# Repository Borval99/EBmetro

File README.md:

# EBmetro

## Descrizione

Il progetto riguarda la ricostruzione di un **misuratore di campi elettrici e magnetici (EBmetro)** ideato dal Prof. Francesco Dalla Valle.

Lo strumento è stato progettato per rendere **misurabili e osservabili**:

* intensità del campo elettrico e magnetico
* direzione
* verso

con l’obiettivo di fornire un supporto concreto alla comprensione dell’elettromagnetismo.

---

## Obiettivo

L’EBmetro permette di verificare sperimentalmente:

* la circuitazione del campo elettrico lungo una linea chiusa
* la circuitazione del campo magnetico
* il fenomeno dell’induzione elettromagnetica

rendendo osservabili in modo diretto le prime tre equazioni di Maxwell.

---

## Struttura della repository

### /3D Model

Contiene i modelli dei case utilizzati per ospitare il microcontrollore e la scheda di acquisizione.

Sono presenti due principali varianti:

* versione per stampa 3D
* versione per taglio laser

La versione realizzata tramite intaglio laser consente una produzione più rapida e semplificata.

---

### /EBmetro

Contiene l’implementazione completa del dispositivo:

* schemi elettronici
* PCB
* firmware

Dove sono presenti le schede per l'EBmetro e per la base dell'EBmetro.

---

### /generatore

Contiene lo sviluppo di un generatore di rampe di corrente:

* schema elettronico
* firmware

Il generatore è in grado di fornire correnti fino a 30 A ed è utilizzato per pilotare bobine di Helmholtz.
Questo consente di generare campi magnetici controllati e misurare, tramite il sensore (“manico”), l’andamento della corrente indotta in un avvolgimento di dimensioni variabili.

---

## Descrizione del funzionamento

Il dispositivo consente la misura del campo elettrico o magnetico in funzione:

* della testina installata
* delle impostazioni software

L’elemento principale è una **testina rotante** dotata di contatti in oro, che ruota sul proprio asse.

I contatti sono stati realizzati tramite PCB, HASL con placcatura.

Durante la rotazione, la testina entra in contatto con due **contatti striscianti**, permettendo l’acquisizione del segnale.

L’elaborazione del segnale avviene in un’unità separata dalla base, al fine di ridurre le interferenze sulla misura.

Nella base dell’EBmetro è possibile integrare:

* un motore brushless
* oppure un motore passo-passo

entrambi controllati da un microcontrollore ATtiny85 posizionato sotto la struttura.

L'EBmetro ha inoltre un Goniometro sulla propria base.

---

## Crediti

Ideato dal:

* Prof. Francesco Dalla Valle
* Prof. Giacomoni
* Prof. Cortesi

Sviluppo di questa versione:

* Enzo Cortesi
* Ing. Valerio Borghi
* FabLab Maker Station Bassa Romagna

---

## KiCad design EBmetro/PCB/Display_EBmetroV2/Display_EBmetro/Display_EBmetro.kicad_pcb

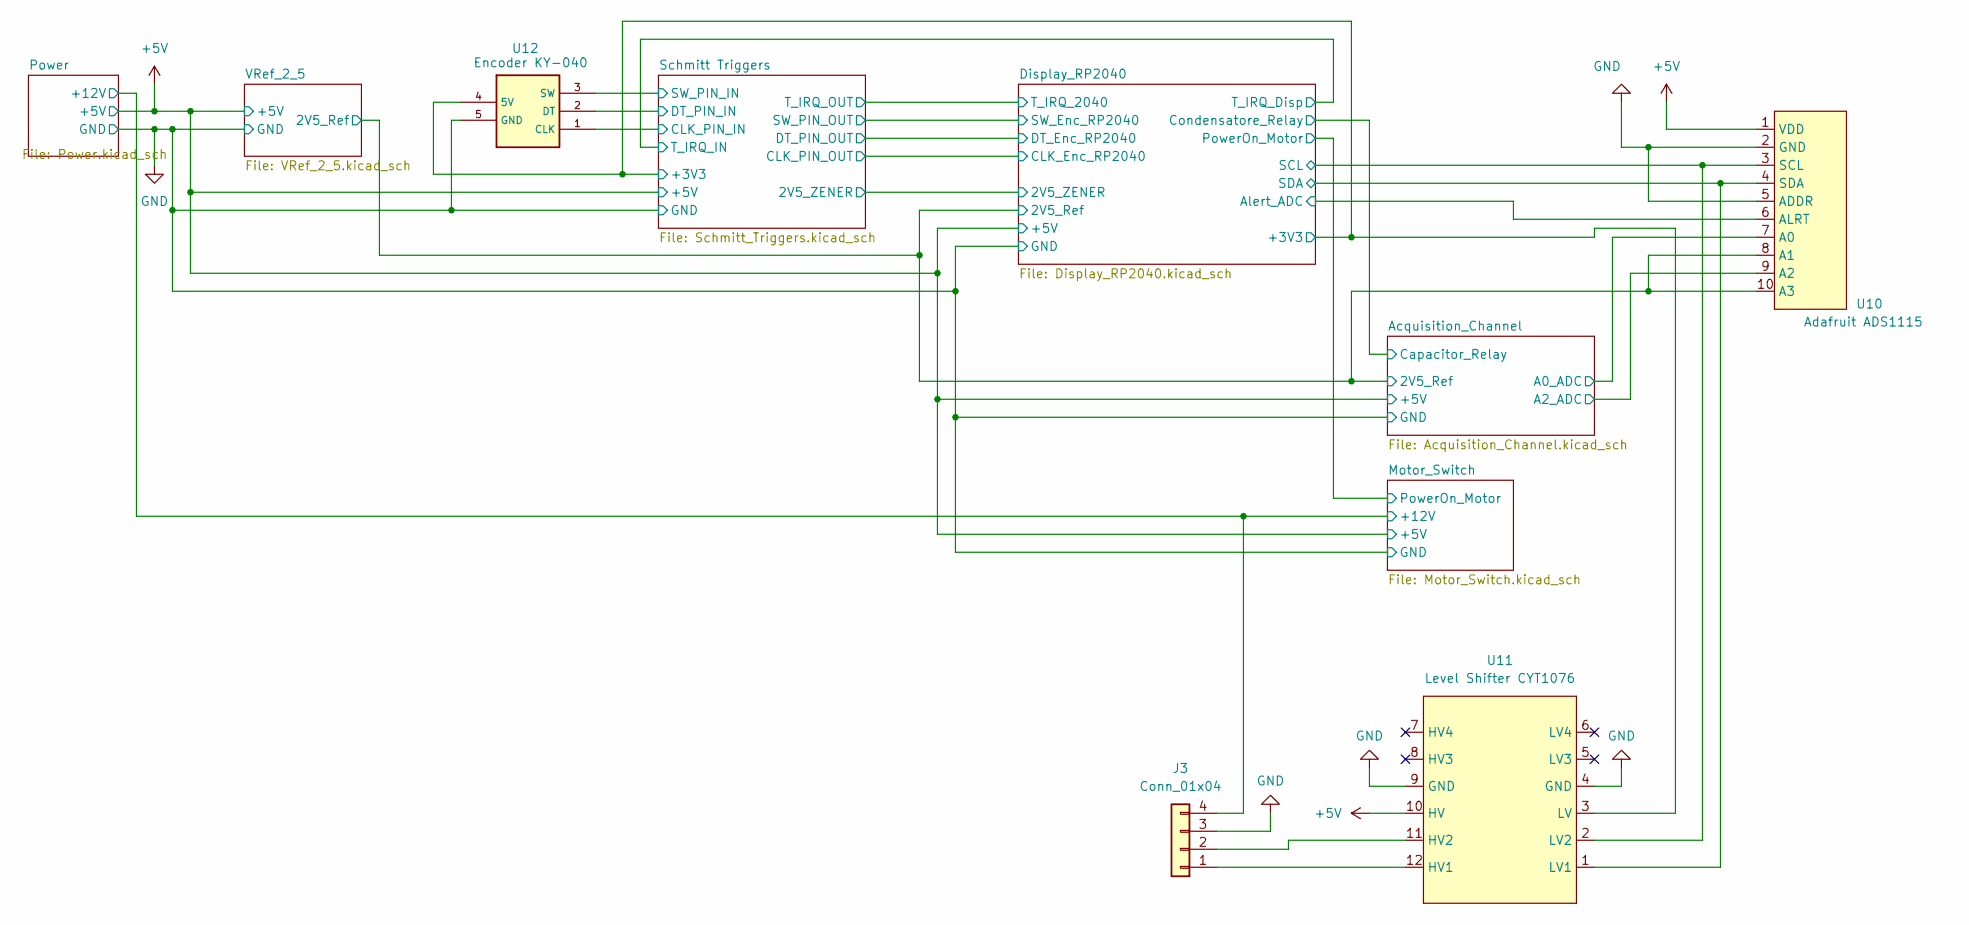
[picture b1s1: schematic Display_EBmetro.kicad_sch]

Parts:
J3: Conn_01x04; JST_EH_B4B-EH-A_1x04_P2.50mm_Vertical
U10: Adafruit ADS1115; PinSocket_1x10_P2.54mm_Vertical
U11: Level Shifter CYT1076; LevelShifter_CYT1076
U12: Encoder KY-040; Encoder_KY-040

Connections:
+5V: U10.1 (VDD), U11.10 (HV); also elsewhere on the board
+12V: J3.4; also elsewhere on the board
/Acquisition_Channel/2V5_Ref: U10.8 (A1), U10.10 (A3); also elsewhere on the board
/Acquisition_Channel/A0_ADC: U10.7 (A0); also elsewhere on the board
/Acquisition_Channel/A2_ADC: U10.9 (A2); also elsewhere on the board
/Display_RP2040/+3V3: U11.3 (LV), U12.4 (5V); also elsewhere on the board
/Display_RP2040/Alert_ADC: U10.6 (ALRT); also elsewhere on the board
/Display_RP2040/SCL: U10.3 (SCL), U11.2 (LV2); also elsewhere on the board
/Display_RP2040/SDA: U10.4 (SDA), U11.1 (LV1); also elsewhere on the board
/Schmitt Triggers/CLK_PIN_IN: U12.1 (CLK); also elsewhere on the board
/Schmitt Triggers/DT_PIN_IN: U12.2 (DT); also elsewhere on the board
/Schmitt Triggers/SW_PIN_IN: U12.3 (SW); also elsewhere on the board
GND: J3.3, U10.2 (GND), U10.5 (ADDR), U11.4 (GND), U11.9 (GND), U12.5 (GND); also elsewhere on the board
unnamed: J3.1, U11.12 (HV1)
unnamed: J3.2, U11.11 (HV2)

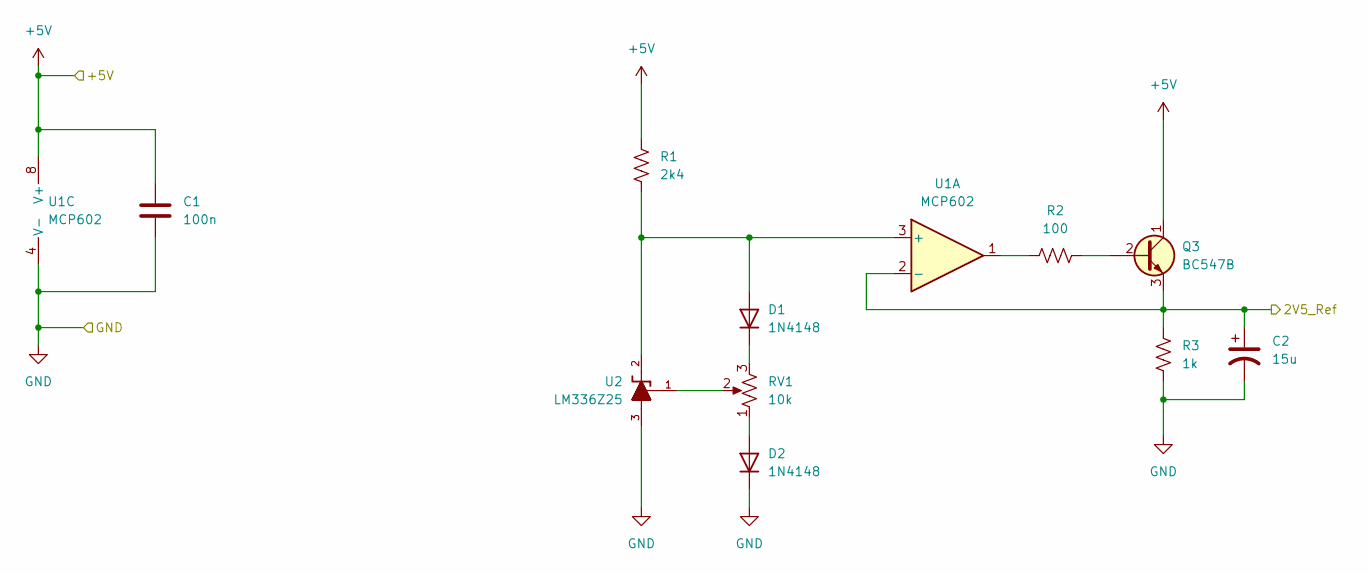
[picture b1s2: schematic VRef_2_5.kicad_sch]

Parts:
C1: 100n; C_Rect_L7.2mm_W2.5mm_P5.00mm_FKS2_FKP2_MKS2_MKP2
C2: 15u; CP_Radial_Tantal_D5.5mm_P5.00mm
D1, D2: 1N4148; D_DO-35_SOD27_P7.62mm_Horizontal
Q3: BC547B; TO-92_Inline_Wide_CBE
R1: 2k4; R_Axial_DIN0207_L6.3mm_D2.5mm_P10.16mm_Horizontal
R2: 100; R_Axial_DIN0207_L6.3mm_D2.5mm_P10.16mm_Horizontal
R3: 1k; R_Axial_DIN0207_L6.3mm_D2.5mm_P10.16mm_Horizontal
RV1: 10k; Potentiometer_Bourns_3296W_Vertical
U1: MCP602; DIP-8_W7.62mm_Socket
U2: LM336Z25; TO-92L_Inline_Wide

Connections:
+5V: C1.2, Q3.1 (C), R1.1, U1.8 (V+); also elsewhere on the board
/Acquisition_Channel/2V5_Ref: C2.1, Q3.3 (E), R3.1, U1.2 (-); also elsewhere on the board
GND: C1.1, C2.2, D2.1 (K), R3.2, U1.4 (V-), U2.3; also elsewhere on the board
unnamed: D1.2 (A), R1.2, U1.3 (+), U2.2
unnamed: D1.1 (K), RV1.3
unnamed: D2.2 (A), RV1.1
unnamed: Q3.2 (B), R2.2
unnamed: R2.1, U1.1
unnamed: RV1.2, U2.1

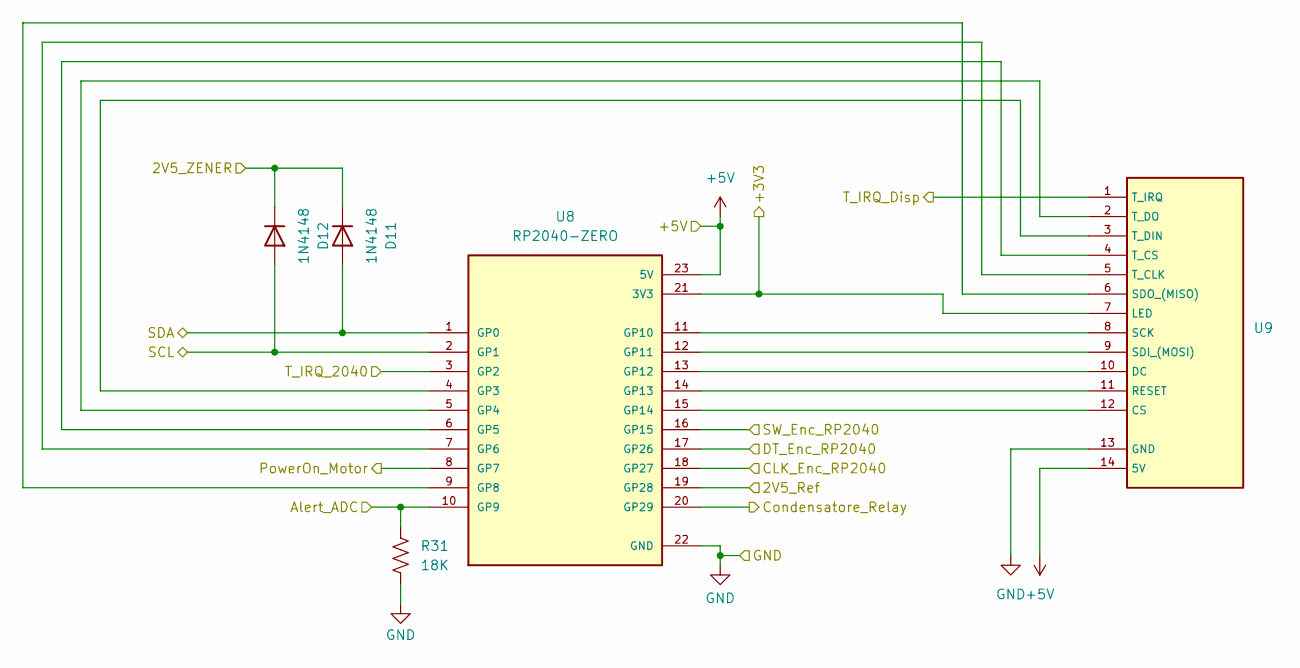
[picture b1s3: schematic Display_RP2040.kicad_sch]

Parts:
D11, D12: 1N4148; D_DO-35_SOD27_P7.62mm_Horizontal
R31: 18K; R_Axial_DIN0207_L6.3mm_D2.5mm_P10.16mm_Horizontal
U8: RP2040-ZERO; MODULE_RP2040-ZERO_V2; PARTREV NA
U9: Display_TFT_LCD_4

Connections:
+5V: U8.23 (5V), U9.14 (5V); also elsewhere on the board
/Acquisition_Channel/2V5_Ref: U8.19 (GP28); also elsewhere on the board
/Acquisition_Channel/Capacitor_Relay: U8.20 (GP29); also elsewhere on the board
/Display_RP2040/+3V3: U8.21 (3V3), U9.7 (LED); also elsewhere on the board
/Display_RP2040/Alert_ADC: R31.1, U8.10 (GP9); also elsewhere on the board
/Display_RP2040/CLK_Enc_RP2040: U8.18 (GP27); also elsewhere on the board
/Display_RP2040/DT_Enc_RP2040: U8.17 (GP26); also elsewhere on the board
/Display_RP2040/PowerOn_Motor: U8.8 (GP7); also elsewhere on the board
/Display_RP2040/SCL: D12.2 (A), U8.2 (GP1); also elsewhere on the board
/Display_RP2040/SDA: D11.2 (A), U8.1 (GP0); also elsewhere on the board
/Display_RP2040/SW_Enc_RP2040: U8.16 (GP15); also elsewhere on the board
/Display_RP2040/T_IRQ_2040: U8.3 (GP2); also elsewhere on the board
/Display_RP2040/T_IRQ_Disp: U9.1 (T_IRQ); also elsewhere on the board
/Schmitt Triggers/2V5_ZENER: D11.1 (K), D12.1 (K); also elsewhere on the board
GND: R31.2, U8.22 (GND), U9.13 (GND); also elsewhere on the board
unnamed: U8.4 (GP3), U9.3 (T_DIN)
unnamed: U8.5 (GP4), U9.2 (T_DO)
unnamed: U8.6 (GP5), U9.4 (T_CS)
unnamed: U8.7 (GP6), U9.5 (T_CLK)
unnamed: U8.9 (GP8), U9.6 (SDO_(MISO))
unnamed: U8.11 (GP10), U9.8 (SCK)
unnamed: U8.12 (GP11), U9.9 (SDI_(MOSI))
unnamed: U8.13 (GP12), U9.10 (DC)
unnamed: U8.14 (GP13), U9.11 (RESET)
unnamed: U8.15 (GP14), U9.12 (CS)

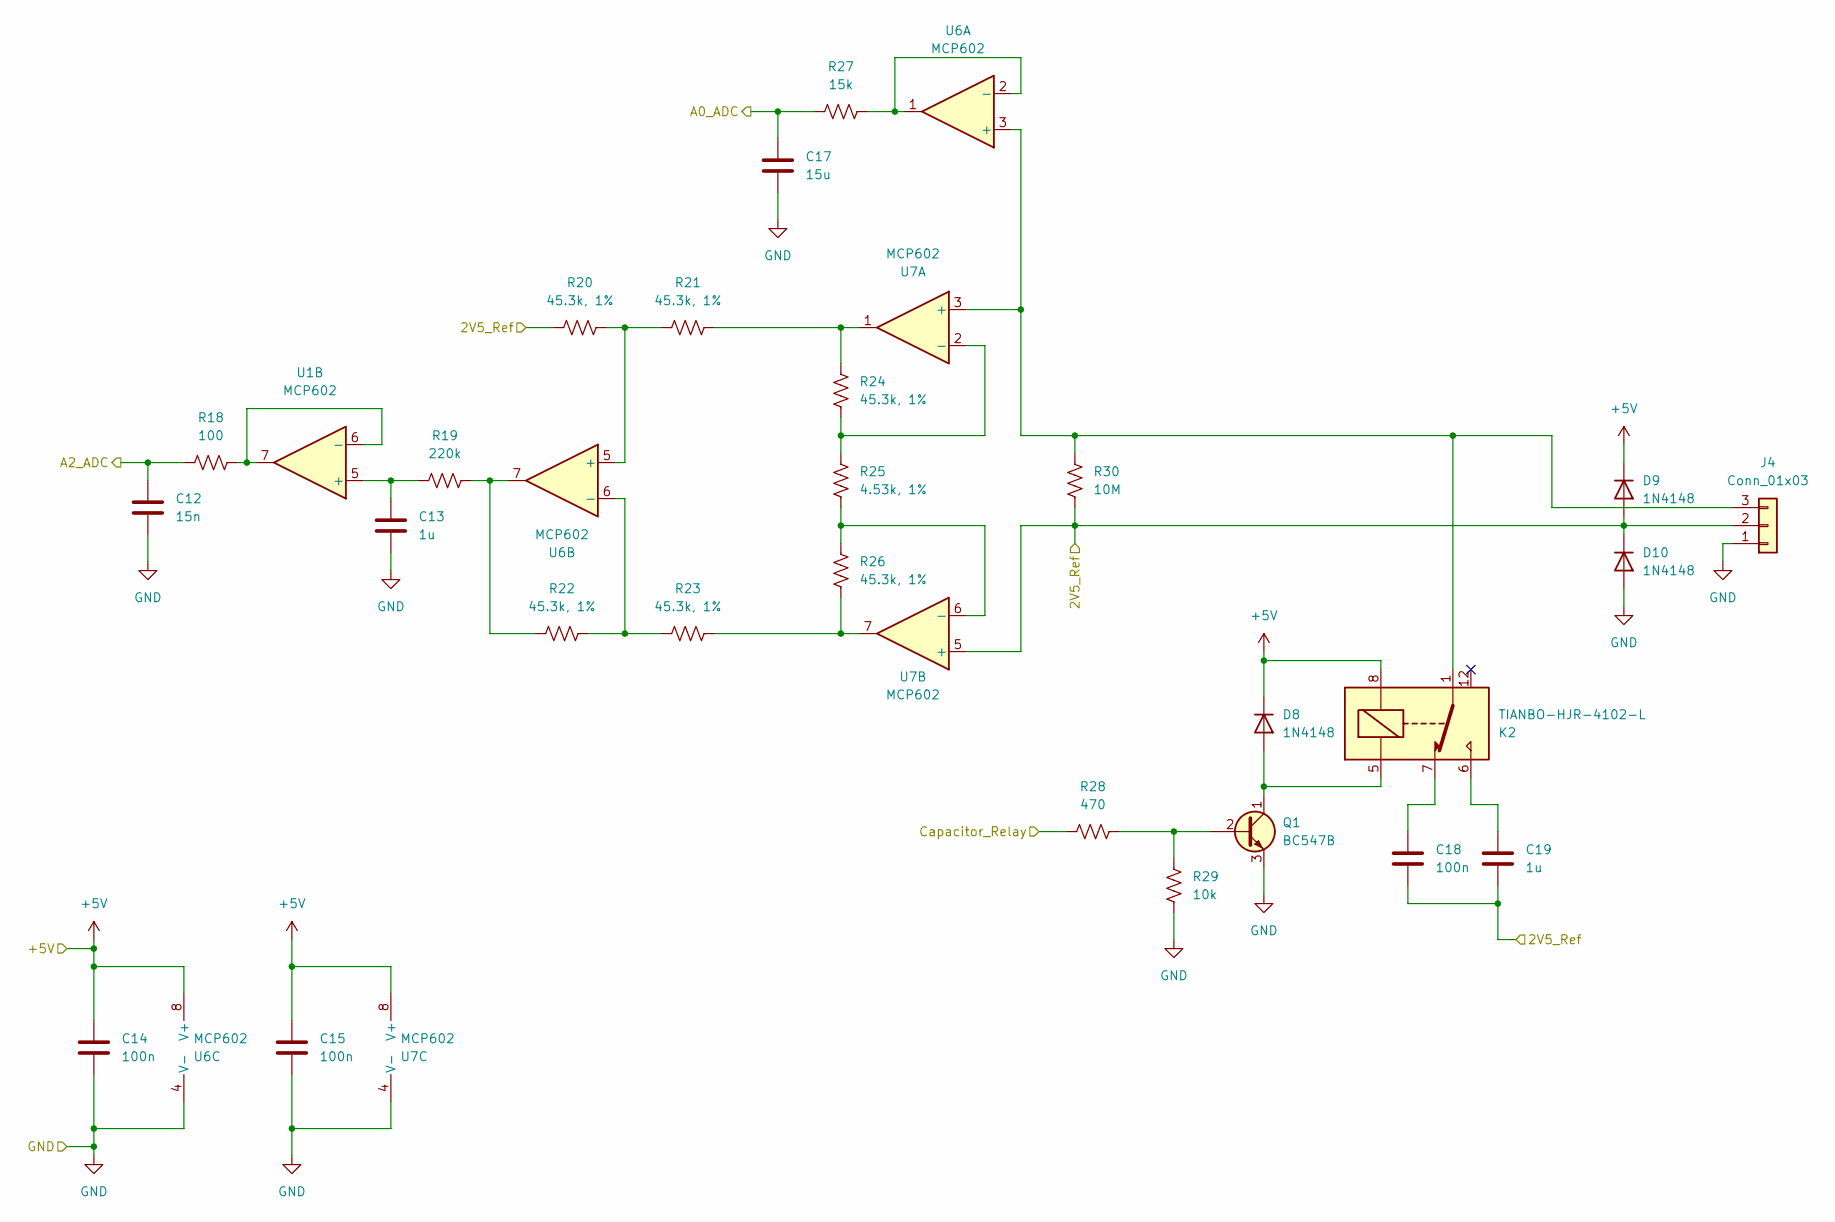
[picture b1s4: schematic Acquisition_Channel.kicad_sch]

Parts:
C12: 15n; C_Rect_L7.2mm_W2.5mm_P5.00mm_FKS2_FKP2_MKS2_MKP2
C13, C19: 1u; C_Rect_L7.2mm_W5.5mm_P5.00mm_FKS2_FKP2_MKS2_MKP2
C14, C15, C18: 100n; C_Rect_L7.2mm_W2.5mm_P5.00mm_FKS2_FKP2_MKS2_MKP2
C17: 15u; C_Rect_L7.2mm_W2.5mm_P5.00mm_FKS2_FKP2_MKS2_MKP2
D8, D9, D10: 1N4148; D_DO-35_SOD27_P7.62mm_Horizontal
J4: Conn_01x03; JST_EH_B3B-EH-A_1x03_P2.50mm_Vertical
K2: TIANBO-HJR-4102-L; Relay_SPDT_HJR-4102
Q1: BC547B; TO-92_Inline_Wide_CBE
R18: 100; R_Axial_DIN0207_L6.3mm_D2.5mm_P10.16mm_Horizontal
R19: 220k; R_Axial_DIN0207_L6.3mm_D2.5mm_P10.16mm_Horizontal
R20, R21, R22, R23, R24, R26: 45.3k, 1%; R_Axial_DIN0207_L6.3mm_D2.5mm_P10.16mm_Horizontal
R25: 4.53k, 1%; R_Axial_DIN0207_L6.3mm_D2.5mm_P10.16mm_Horizontal
R27: 15k; R_Axial_DIN0207_L6.3mm_D2.5mm_P10.16mm_Horizontal
R28: 470; R_Axial_DIN0207_L6.3mm_D2.5mm_P10.16mm_Horizontal
R29: 10k; R_Axial_DIN0207_L6.3mm_D2.5mm_P10.16mm_Horizontal
R30: 10M; R_Axial_DIN0207_L6.3mm_D2.5mm_P10.16mm_Horizontal
U1, U6, U7: MCP602; DIP-8_W7.62mm_Socket

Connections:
+5V: C14.1, C15.1, D8.1 (K), D9.1 (K), K2.8, U6.8 (V+), U7.8 (V+); also elsewhere on the board
/Acquisition_Channel/2V5_Ref: C18.2, C19.2, D9.2 (A), D10.1 (K), J4.2, R20.1, R30.2, U7.5 (+); also elsewhere on the board
/Acquisition_Channel/A0_ADC: C17.1, R27.2; also elsewhere on the board
/Acquisition_Channel/A2_ADC: C12.1, R18.1; also elsewhere on the board
/Acquisition_Channel/Capacitor_Relay: R28.2; also elsewhere on the board
GND: C12.2, C13.2, C14.2, C15.2, C17.2, D10.2 (A), J4.1, Q1.3 (E), R29.2, U6.4 (V-), U7.4 (V-); also elsewhere on the board
unnamed: C18.1, K2.7
unnamed: C19.1, K2.6
unnamed: D8.2 (A), K2.5, Q1.1 (C)
unnamed: J4.3, K2.1, R30.1, U6.3 (+), U7.3 (+)
unnamed: Q1.2 (B), R28.1, R29.1
unnamed: R19.2, R22.1, U6.7
unnamed: R21.2, R24.2, U7.1
unnamed: R23.2, R26.1, U7.7
unnamed: C13.1, R19.1, U1.5 (+)
unnamed: R18.2, U1.6 (-), U1.7
unnamed: R27.1, U6.1, U6.2 (-)
unnamed: R20.2, R21.1, U6.5 (+)
unnamed: R22.2, R23.1, U6.6 (-)
unnamed: R24.1, R25.2, U7.2 (-)
unnamed: R25.1, R26.2, U7.6 (-)

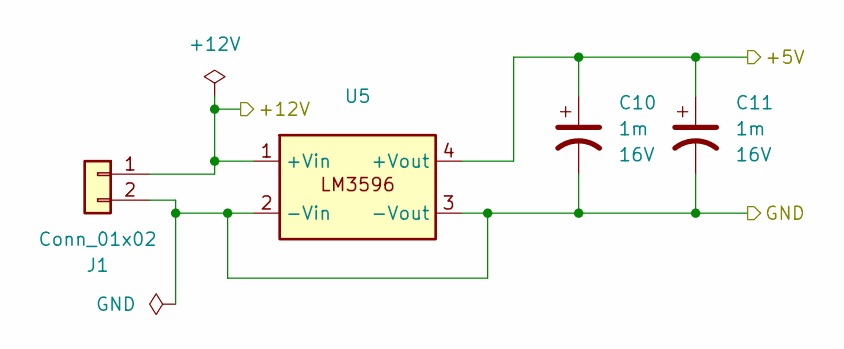
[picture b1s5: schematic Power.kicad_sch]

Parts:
C10, C11: 1m; CP_Radial_D10.0mm_P5.00mm; Voltage 16V
J1: Conn_01x02; JST_EH_B2B-EH-A_1x02_P2.50mm_Vertical
U5: LM3596

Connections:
+5V: C10.1, C11.1, U5.4 (+Vout); also elsewhere on the board
+12V: J1.1, U5.1 (+Vin); also elsewhere on the board
GND: C10.2, C11.2, J1.2, U5.2 (-Vin), U5.3 (-Vout); also elsewhere on the board

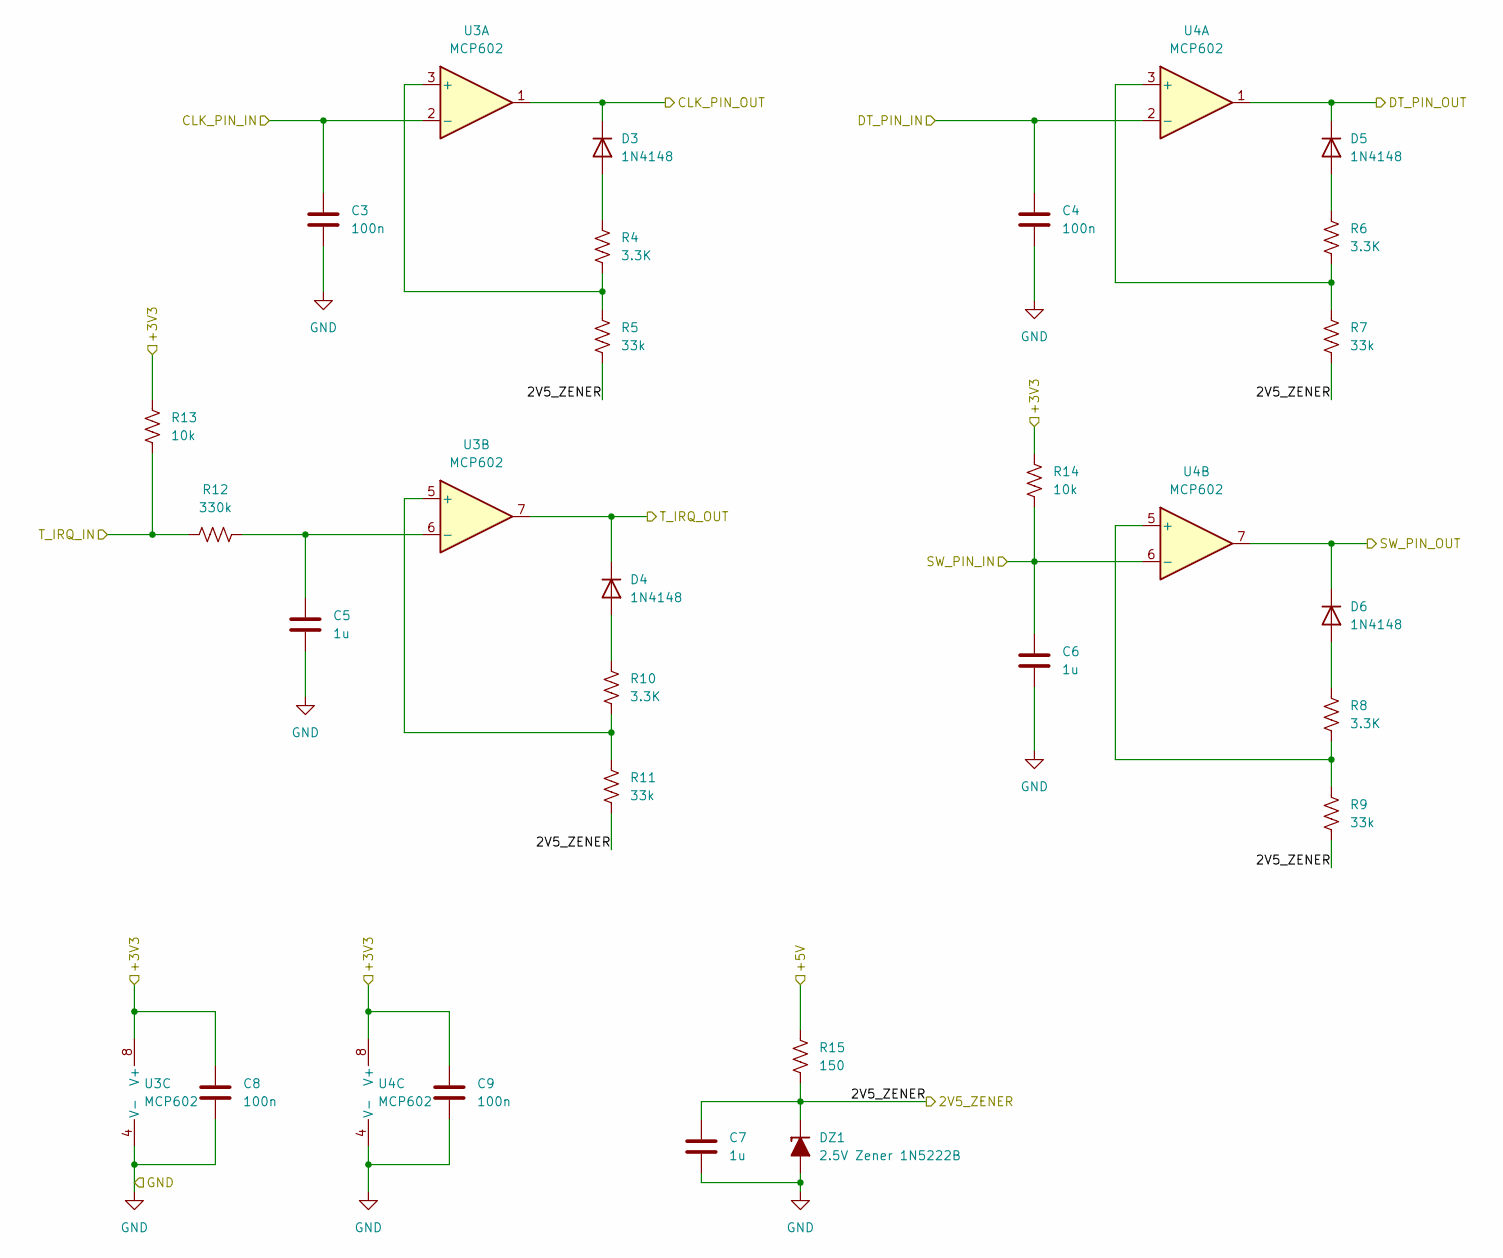
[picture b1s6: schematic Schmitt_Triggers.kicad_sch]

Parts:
C3, C4, C8, C9: 100n; C_Rect_L7.2mm_W2.5mm_P5.00mm_FKS2_FKP2_MKS2_MKP2
C5, C6, C7: 1u; C_Rect_L7.2mm_W5.5mm_P5.00mm_FKS2_FKP2_MKS2_MKP2
D3, D4, D5, D6: 1N4148; D_DO-35_SOD27_P7.62mm_Horizontal
DZ1: 2.5V Zener 1N5222B; D_DO-35_SOD27_P10.16mm_Horizontal_Zener
R4, R6, R8, R10: 3.3K; R_Axial_DIN0207_L6.3mm_D2.5mm_P10.16mm_Horizontal
R5, R7, R9, R11: 33k; R_Axial_DIN0207_L6.3mm_D2.5mm_P10.16mm_Horizontal
R12: 330k; R_Axial_DIN0207_L6.3mm_D2.5mm_P10.16mm_Horizontal
R13, R14: 10k; R_Axial_DIN0207_L6.3mm_D2.5mm_P10.16mm_Horizontal
R15: 150; R_Axial_DIN0207_L6.3mm_D2.5mm_P10.16mm_Horizontal
U3, U4: MCP602; DIP-8_W7.62mm_Socket

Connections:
+5V: R15.1; also elsewhere on the board
/Display_RP2040/+3V3: C8.1, C9.1, R13.2, R14.1, U3.8 (V+), U4.8 (V+); also elsewhere on the board
/Display_RP2040/CLK_Enc_RP2040: D3.1 (K), U3.1; also elsewhere on the board
/Display_RP2040/DT_Enc_RP2040: D5.1 (K), U4.1; also elsewhere on the board
/Display_RP2040/SW_Enc_RP2040: D6.1 (K), U4.7; also elsewhere on the board
/Display_RP2040/T_IRQ_2040: D4.1 (K), U3.7; also elsewhere on the board
/Display_RP2040/T_IRQ_Disp: R12.2, R13.1; also elsewhere on the board
/Schmitt Triggers/2V5_ZENER: C7.1, DZ1.1 (K), R5.2, R7.2, R9.2, R11.2, R15.2; also elsewhere on the board
/Schmitt Triggers/CLK_PIN_IN: C3.1, U3.2 (-); also elsewhere on the board
/Schmitt Triggers/DT_PIN_IN: C4.1, U4.2 (-); also elsewhere on the board
/Schmitt Triggers/SW_PIN_IN: C6.1, R14.2, U4.6 (-); also elsewhere on the board
GND: C3.2, C4.2, C5.2, C6.2, C7.2, C8.2, C9.2, DZ1.2 (A), U3.4 (V-), U4.4 (V-); also elsewhere on the board
unnamed: D3.2 (A), R4.1
unnamed: D4.2 (A), R10.1
unnamed: D5.2 (A), R6.1
unnamed: D6.2 (A), R8.1
unnamed: R4.2, R5.1, U3.3 (+)
unnamed: R10.2, R11.1, U3.5 (+)
unnamed: C5.1, R12.1, U3.6 (-)
unnamed: R6.2, R7.1, U4.3 (+)
unnamed: R8.2, R9.1, U4.5 (+)

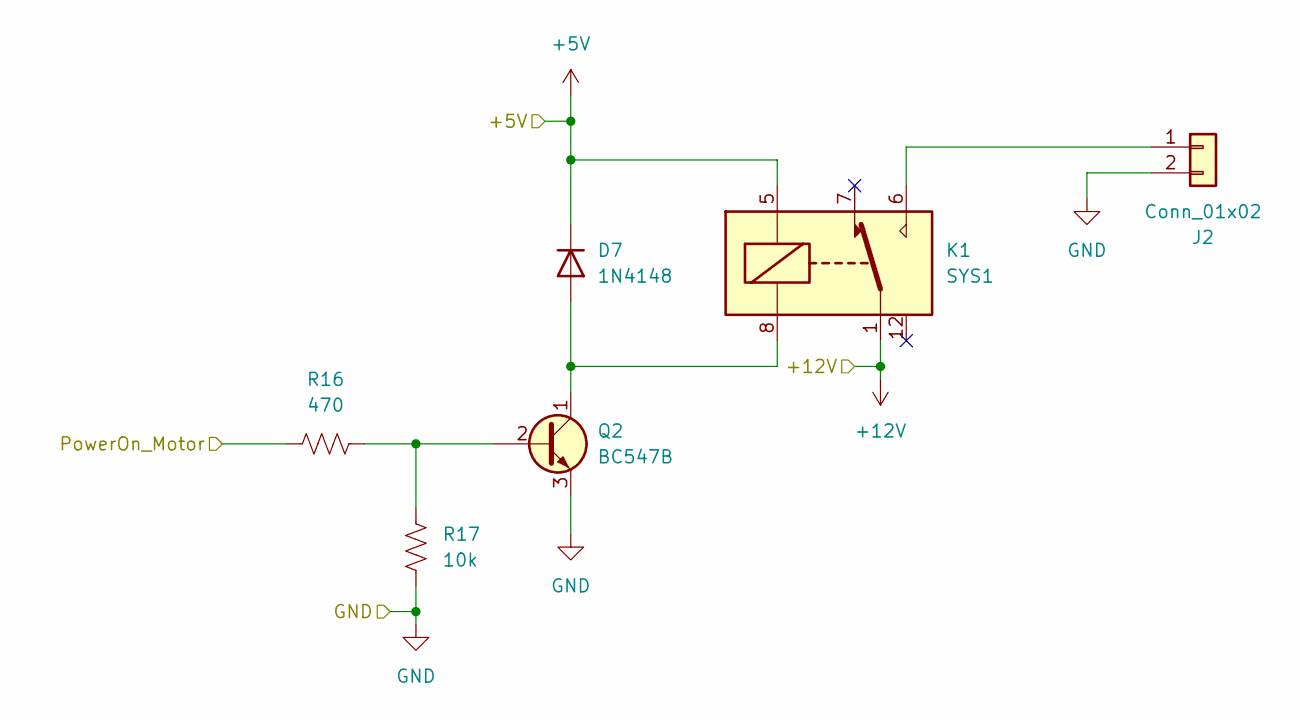
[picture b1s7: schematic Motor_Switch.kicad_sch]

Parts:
D7: 1N4148; D_DO-35_SOD27_P7.62mm_Horizontal
J2: Conn_01x02; JST_EH_B2B-EH-A_1x02_P2.50mm_Vertical
K1: SYS1; Relay_SPDT_HJR-4102
Q2: BC547B; TO-92_Inline_Wide_CBE
R16: 470; R_Axial_DIN0207_L6.3mm_D2.5mm_P10.16mm_Horizontal
R17: 10k; R_Axial_DIN0207_L6.3mm_D2.5mm_P10.16mm_Horizontal

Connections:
+5V: D7.1 (K), K1.5; also elsewhere on the board
+12V: K1.1; also elsewhere on the board
/Display_RP2040/PowerOn_Motor: R16.1; also elsewhere on the board
GND: J2.2, Q2.3 (E), R17.1; also elsewhere on the board
unnamed: D7.2 (A), K1.8, Q2.1 (C)
unnamed: J2.1, K1.6
unnamed: Q2.2 (B), R16.2, R17.2

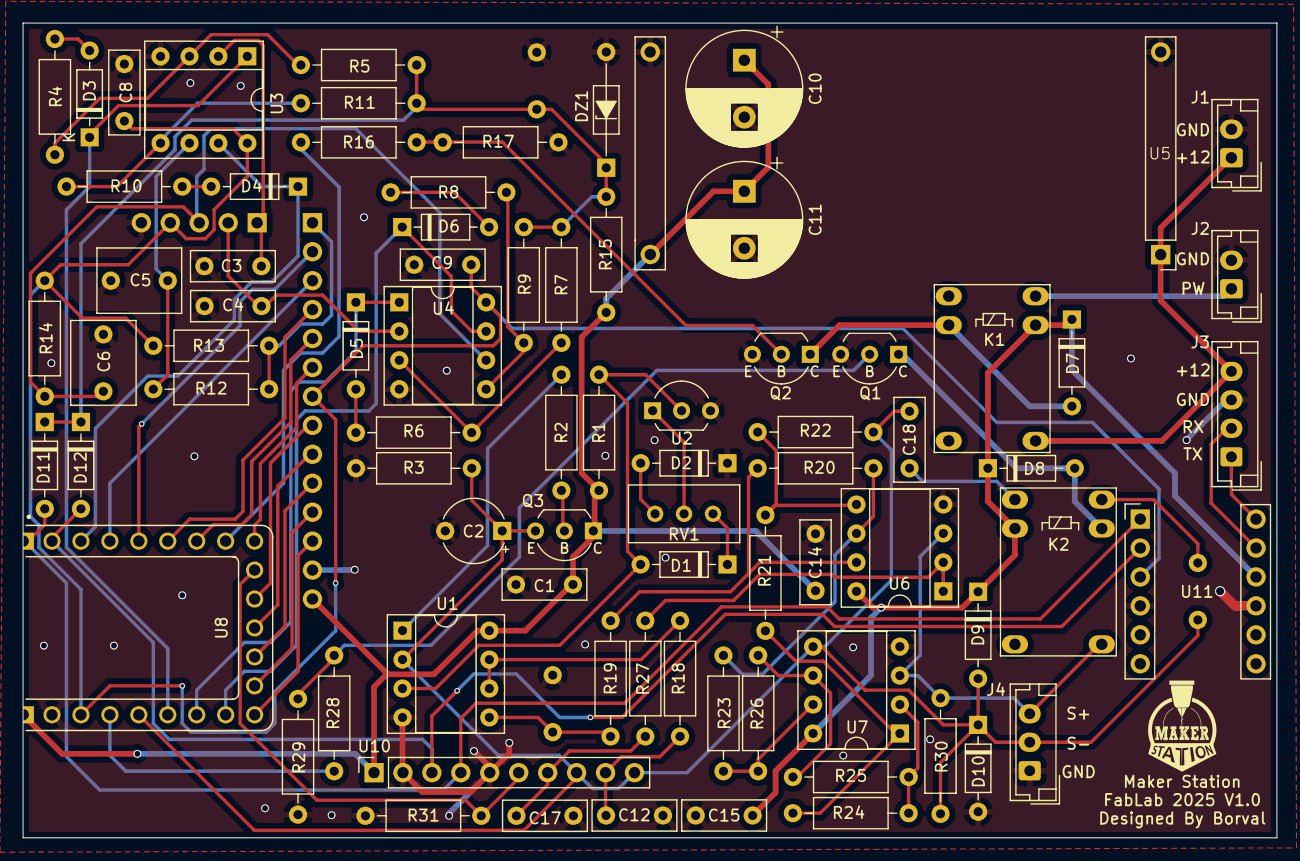
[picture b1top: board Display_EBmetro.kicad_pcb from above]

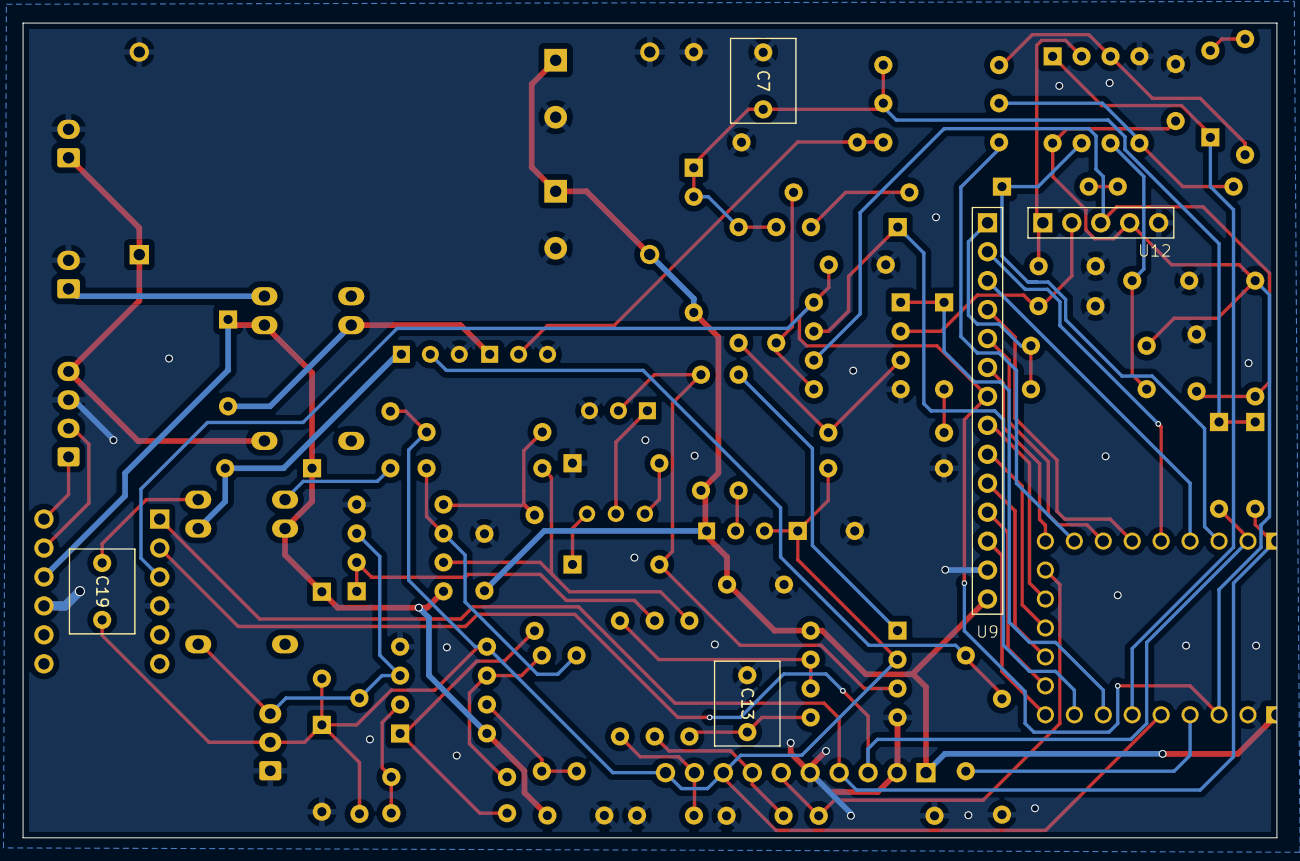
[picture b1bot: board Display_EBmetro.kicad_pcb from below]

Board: 2 copper layers, 110.0 x 71.5 mm, 84 parts (5 on the bottom side), 66 nets.

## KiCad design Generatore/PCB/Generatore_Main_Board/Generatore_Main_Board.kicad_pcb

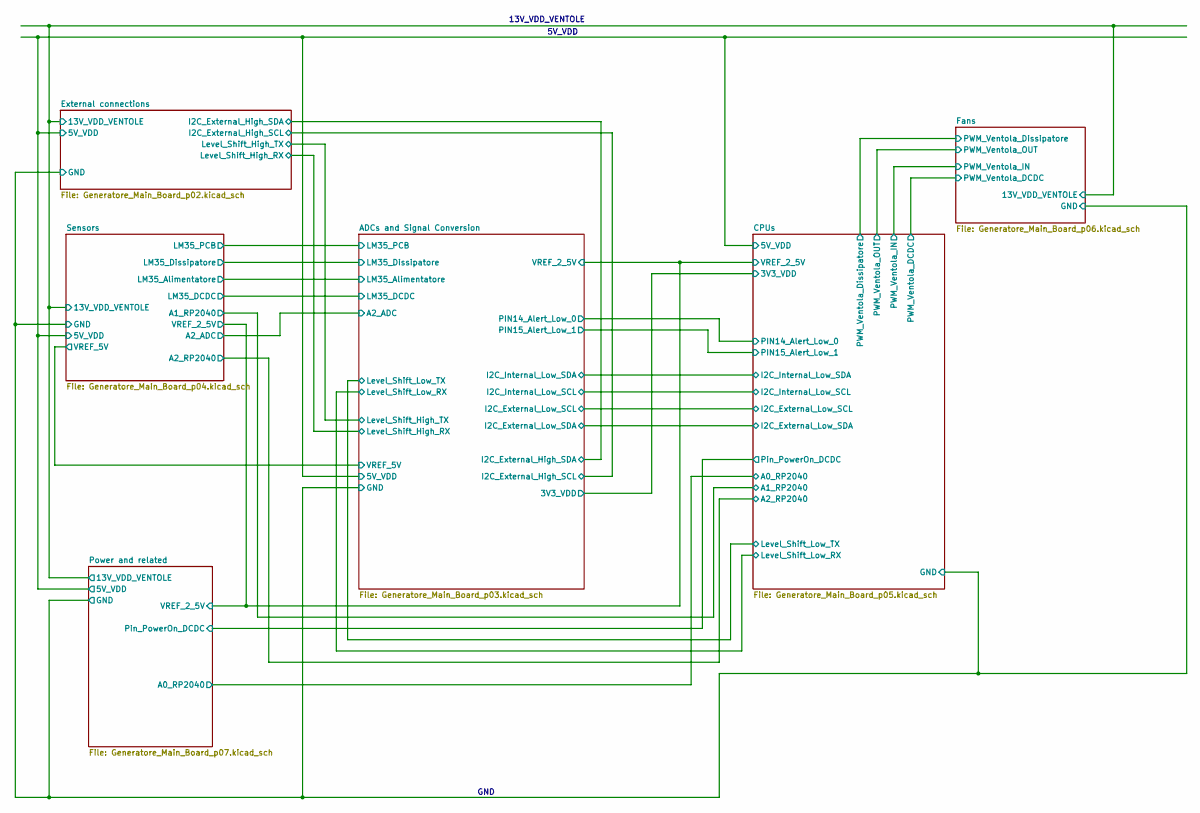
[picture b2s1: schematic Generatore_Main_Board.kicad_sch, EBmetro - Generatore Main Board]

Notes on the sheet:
13V_VDD_VENTOLE
GND
5V_VDD

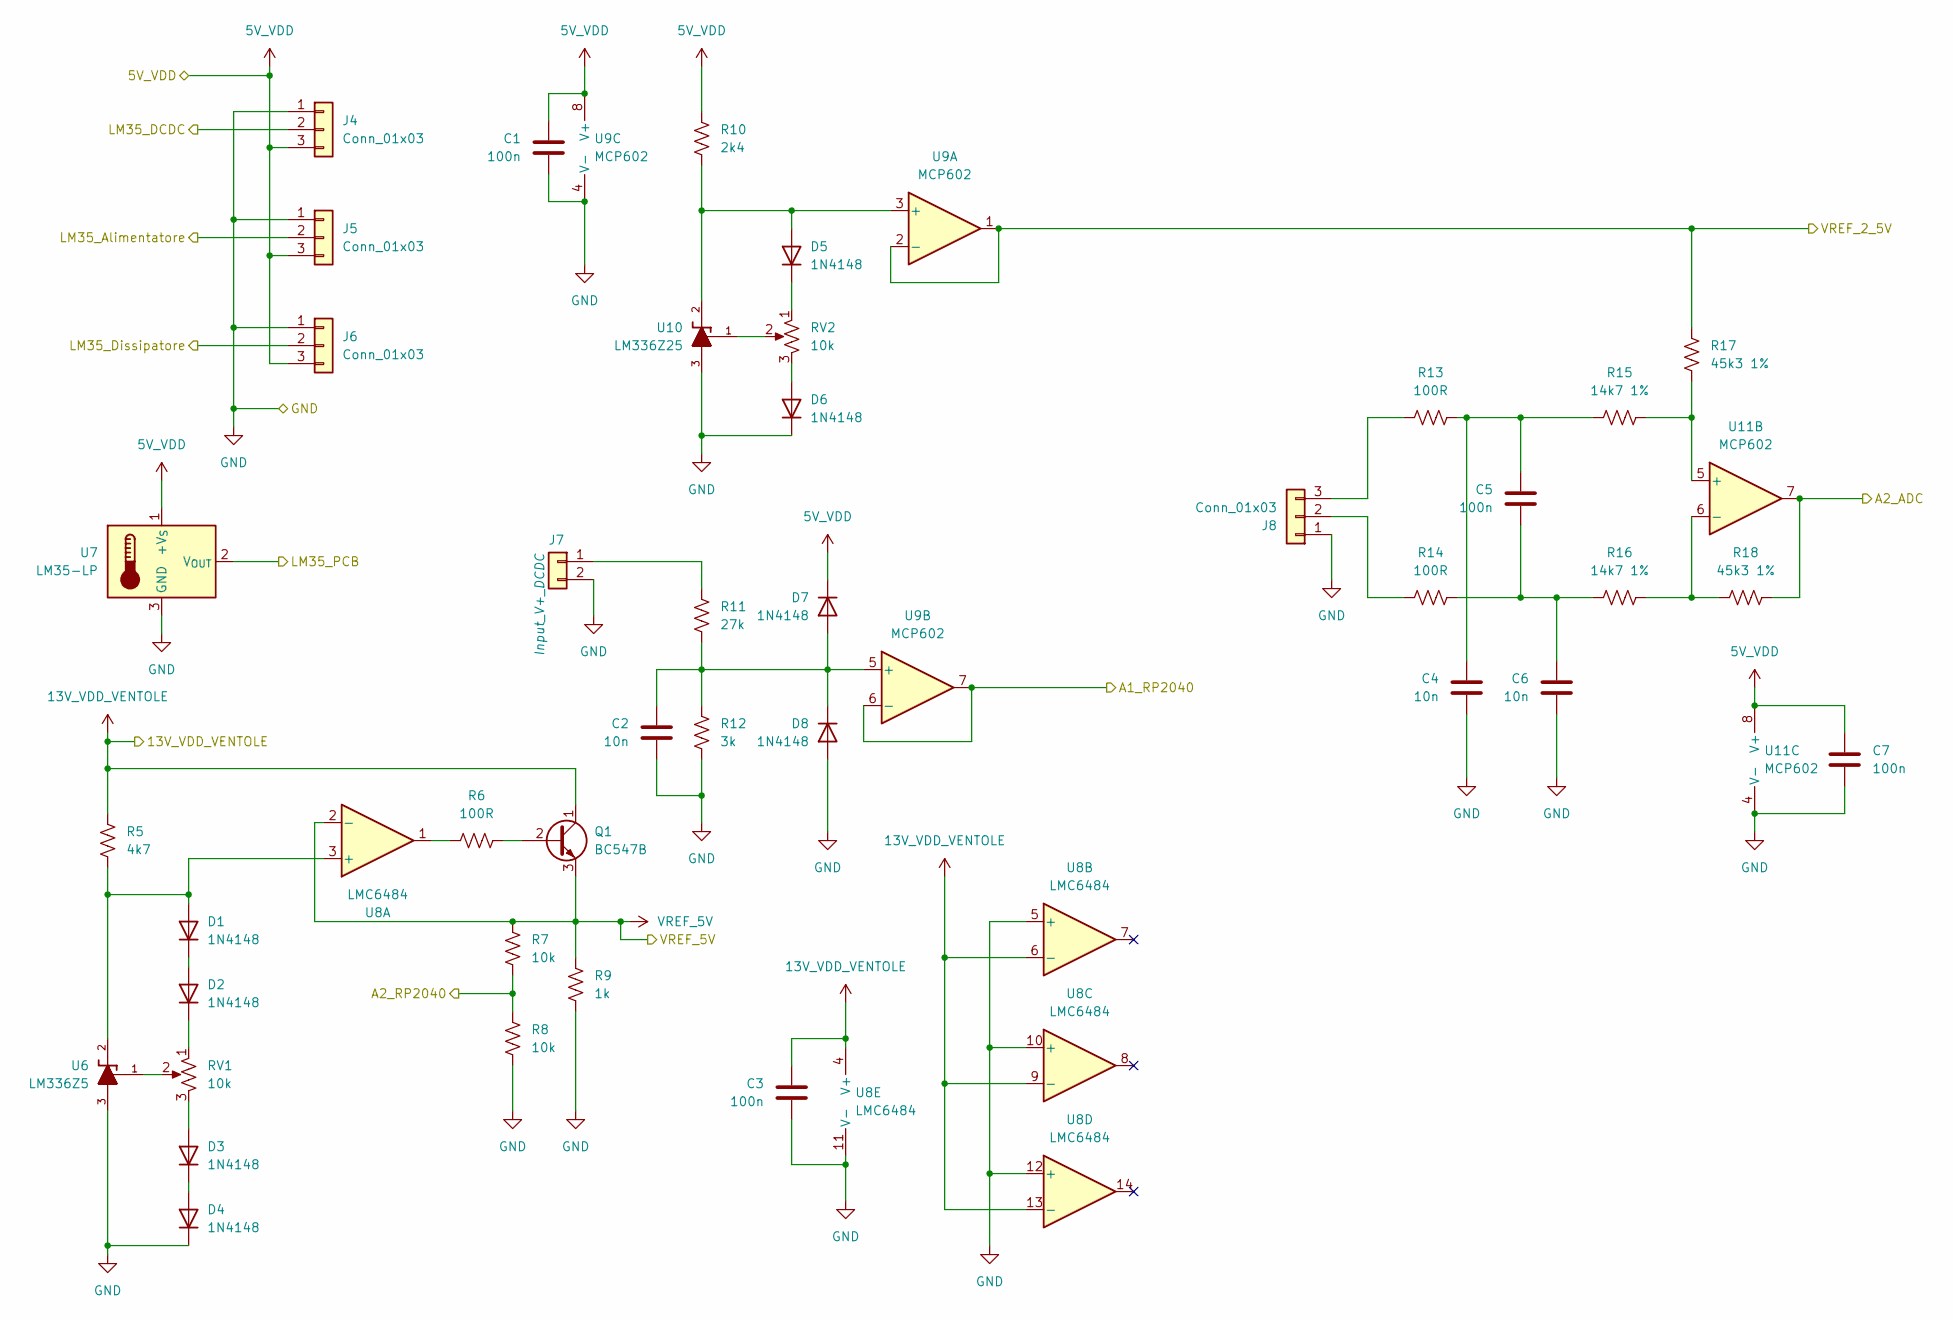
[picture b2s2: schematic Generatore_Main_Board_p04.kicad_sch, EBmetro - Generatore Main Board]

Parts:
C1, C3, C5, C7: 100n; Term_Block_1x2_P5mm
C2, C4, C6: 10n; Term_Block_1x2_P5mm
D1, D2, D3, D4, D5, D6, D7, D8: 1N4148; D_DO-35_SOD27_P7.62mm_Horizontal
J4, J5, J6, J8: Conn_01x03; JST_EH_B3B-EH-A_1x03_P2.50mm_Vertical
J7: Conn_01x02; JST_EH_B2B-EH-A_1x02_P2.50mm_Vertical
Q1: BC547B; TO-92_Inline
R5: 4k7; R_Axial_DIN0207_L6.3mm_D2.5mm_P10.16mm_Horizontal
R6, R13, R14: 100R; R_Axial_DIN0207_L6.3mm_D2.5mm_P10.16mm_Horizontal
R7, R8: 10k; R_Axial_DIN0207_L6.3mm_D2.5mm_P10.16mm_Horizontal
R9: 1k; R_Axial_DIN0207_L6.3mm_D2.5mm_P10.16mm_Horizontal
R10: 2k4; R_Axial_DIN0207_L6.3mm_D2.5mm_P10.16mm_Horizontal
R11: 27k; R_Axial_DIN0207_L6.3mm_D2.5mm_P10.16mm_Horizontal
R12: 3k; R_Axial_DIN0207_L6.3mm_D2.5mm_P10.16mm_Horizontal
R15, R16: 14k7 1%; R_Axial_DIN0207_L6.3mm_D2.5mm_P10.16mm_Horizontal
R17, R18: 45k3 1%; R_Axial_DIN0207_L6.3mm_D2.5mm_P10.16mm_Horizontal
RV1, RV2: 10k; Potentiometer_Bourns_3296W_Vertical
U6: LM336Z5; TO-92-TO92-254P520H877-3
U7: LM35-LP; TO-92_Inline
U8: LMC6484; CERDIP-14_W7.62mm_SideBrazed_LongPads_Socket
U9, U11: MCP602; CERDIP-8_W7.62mm_SideBrazed_LongPads_Socket
U10: LM336Z25; TO-92-TO92-254P520H877-3

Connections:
5V_VDD: C1.1, C7.1, D7.1 (K), J4.3, J5.3, J6.3, R10.1, U7.1 (+V_{S}), U9.8 (V+), U11.8 (V+); also elsewhere on the board
13V_VDD_VENTOLE: C3.1, Q1.1 (C), R5.1, U8.4 (V+), U8.6 (-), U8.9 (-), U8.13 (-); also elsewhere on the board
/ADCs and Signal Conversion/A2_ADC: R18.1, U11.7; also elsewhere on the board
/ADCs and Signal Conversion/LM35_Alimentatore: J5.2; also elsewhere on the board
/ADCs and Signal Conversion/LM35_DCDC: J4.2; also elsewhere on the board
/ADCs and Signal Conversion/LM35_Dissipatore: J6.2; also elsewhere on the board
/ADCs and Signal Conversion/LM35_PCB: U7.2 (V_{OUT}); also elsewhere on the board
/ADCs and Signal Conversion/VREF_2_5V: R17.1, U9.1, U9.2 (-); also elsewhere on the board
/CPUs/A1_RP2040: U9.6 (-), U9.7; also elsewhere on the board
/CPUs/A2_RP2040: R7.2, R8.1; also elsewhere on the board
GND: C1.2, C2.2, C3.2, C4.2, C6.2, C7.2, D4.1 (K), D6.1 (K), D8.2 (A), J4.1, J5.1, J6.1, J7.2, J8.1, R8.2, R9.2, R12.2, U6.3, U7.3 (GND), U8.5 (+), U8.10 (+), U8.11 (V-), U8.12 (+), U9.4 (V-), U10.3, U11.4 (V-); also elsewhere on the board
unnamed: C4.1, C5.1, R13.2, R15.1
unnamed: C5.2, C6.1, R14.2, R16.1
unnamed: D1.2 (A), R5.2, U6.2, U8.3 (+)
unnamed: D1.1 (K), D2.2 (A)
unnamed: D2.1 (K), RV1.1
unnamed: D3.2 (A), RV1.3
unnamed: D3.1 (K), D4.2 (A)
unnamed: D5.2 (A), R10.2, U9.3 (+), U10.2
unnamed: D5.1 (K), RV2.1
unnamed: D6.2 (A), RV2.3
unnamed: C2.1, D7.2 (A), D8.1 (K), R11.2, R12.1, U9.5 (+)
unnamed: J7.1, R11.1
unnamed: J8.2, R14.1
unnamed: J8.3, R13.1
unnamed: Q1.2 (B), R6.2
unnamed: R6.1, U8.1
unnamed: RV1.2, U6.1
unnamed: RV2.2, U10.1
unnamed: R15.2, R17.2, U11.5 (+)
unnamed: R16.2, R18.2, U11.6 (-)
VREF_5V: Q1.3 (E), R7.1, R9.1, U8.2 (-); also elsewhere on the board
